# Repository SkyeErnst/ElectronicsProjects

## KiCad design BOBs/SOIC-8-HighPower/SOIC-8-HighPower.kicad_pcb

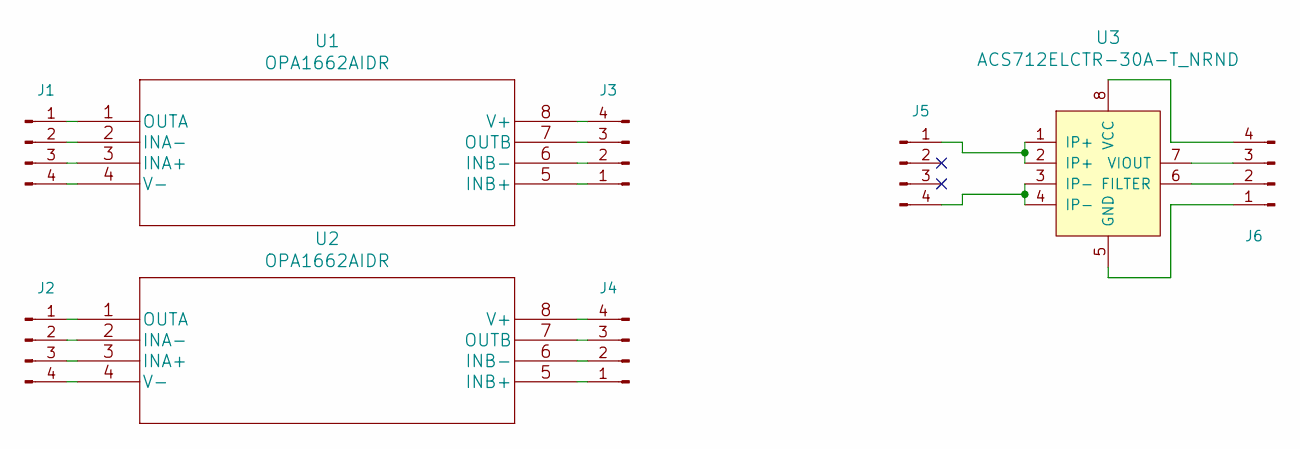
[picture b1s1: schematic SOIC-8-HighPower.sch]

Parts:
J1, J2, J3, J4, J5, J6: Conn_01x04_Male; PinHeader_1x04_P2.54mm_Vertical
U1, U2: OPA1662AIDR; SOIC-8_3.9x4.9mm_P1.27mm
U3: ACS712ELCTR-30A-T_NRND; SOIC-8_3.9x4.9mm_P1.27mm; MPN ACS712ELCTR-30A-T; Digi-Key_PN 620-1191-1-ND

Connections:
unnamed: J1.1, U1.1 (OUTA)
unnamed: J1.2, U1.2 (INA-)
unnamed: J1.3, U1.3 (INA+)
unnamed: J1.4, U1.4 (V-)
unnamed: J2.1, U2.1 (OUTA)
unnamed: J2.2, U2.2 (INA-)
unnamed: J2.3, U2.3 (INA+)
unnamed: J2.4, U2.4 (V-)
unnamed: J3.1, U1.5 (INB+)
unnamed: J3.2, U1.6 (INB-)
unnamed: J3.3, U1.7 (OUTB)
unnamed: J3.4, U1.8 (V+)
unnamed: J4.1, U2.5 (INB+)
unnamed: J4.2, U2.6 (INB-)
unnamed: J4.3, U2.7 (OUTB)
unnamed: J4.4, U2.8 (V+)
unnamed: J5.1, U3.1 (IP+), U3.2 (IP+)
unnamed: J5.4, U3.3 (IP-), U3.4 (IP-)
unnamed: J6.1, U3.5 (GND)
unnamed: J6.2, U3.6 (FILTER)
unnamed: J6.3, U3.7 (VIOUT)
unnamed: J6.4, U3.8 (VCC)

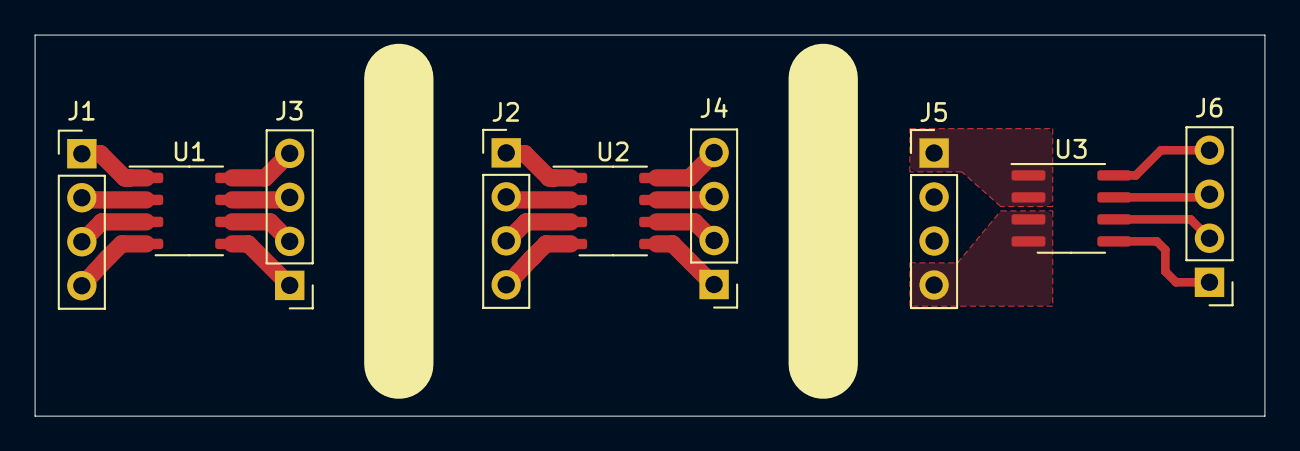
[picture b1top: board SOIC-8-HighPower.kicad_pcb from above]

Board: 2 copper layers, 71.0 x 22.0 mm, 9 parts (0 on the bottom side), 22 nets.

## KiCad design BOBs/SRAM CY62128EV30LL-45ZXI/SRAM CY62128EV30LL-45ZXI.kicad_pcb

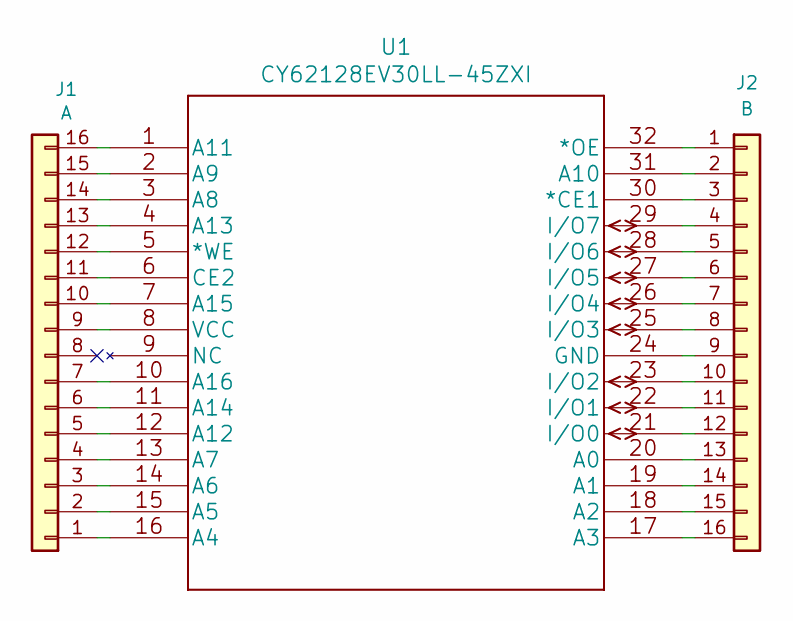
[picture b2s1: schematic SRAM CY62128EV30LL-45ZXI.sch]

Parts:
J1: A; PinHeader_1x16_P2.54mm_Vertical
J2: B; PinHeader_1x16_P2.54mm_Vertical
U1: CY62128EV30LL-45ZXI; TSOP-I-32_18.4x8mm_P0.5mm

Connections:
unnamed: J1.1, U1.16 (A4)
unnamed: J1.2, U1.15 (A5)
unnamed: J1.3, U1.14 (A6)
unnamed: J1.4, U1.13 (A7)
unnamed: J1.5, U1.12 (A12)
unnamed: J1.6, U1.11 (A14)
unnamed: J1.7, U1.10 (A16)
unnamed: J1.9, U1.8 (VCC)
unnamed: J1.10, U1.7 (A15)
unnamed: J1.11, U1.6 (CE2)
unnamed: J1.12, U1.5 (*WE)
unnamed: J1.13, U1.4 (A13)
unnamed: J1.14, U1.3 (A8)
unnamed: J1.15, U1.2 (A9)
unnamed: J1.16, U1.1 (A11)
unnamed: J2.1, U1.32 (*OE)
unnamed: J2.2, U1.31 (A10)
unnamed: J2.3, U1.30 (*CE1)
unnamed: J2.4, U1.29 (I/O7)
unnamed: J2.5, U1.28 (I/O6)
unnamed: J2.6, U1.27 (I/O5)
unnamed: J2.7, U1.26 (I/O4)
unnamed: J2.8, U1.25 (I/O3)
unnamed: J2.9, U1.24 (GND)
unnamed: J2.10, U1.23 (I/O2)
unnamed: J2.11, U1.22 (I/O1)
unnamed: J2.12, U1.21 (I/O0)
unnamed: J2.13, U1.20 (A0)
unnamed: J2.14, U1.19 (A1)
unnamed: J2.15, U1.18 (A2)
unnamed: J2.16, U1.17 (A3)

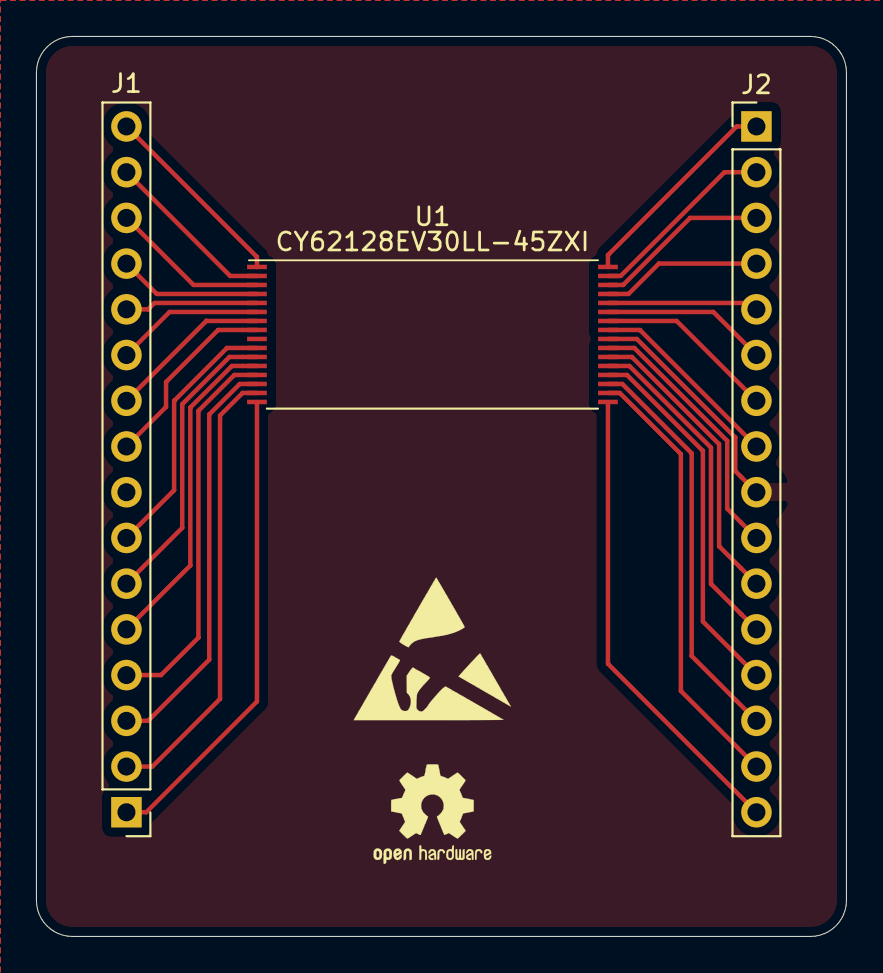
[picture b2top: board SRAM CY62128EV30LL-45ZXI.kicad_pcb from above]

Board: 2 copper layers, 45.0 x 50.0 mm, 3 parts (0 on the bottom side), 31 nets.

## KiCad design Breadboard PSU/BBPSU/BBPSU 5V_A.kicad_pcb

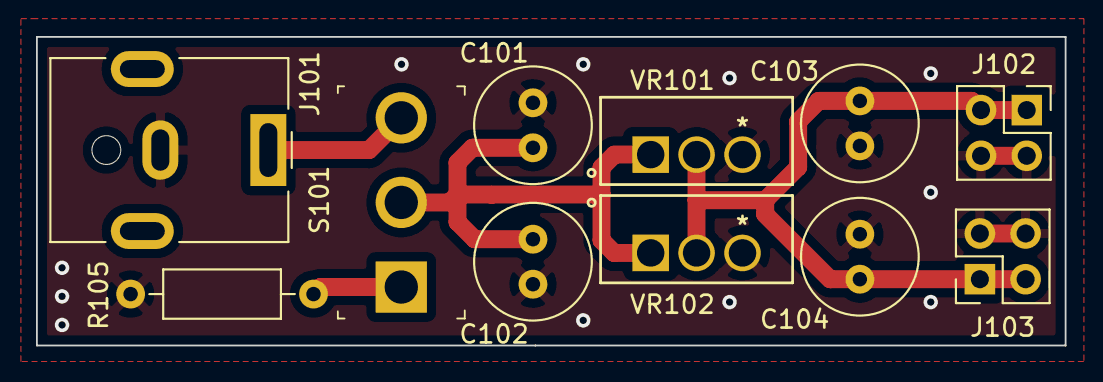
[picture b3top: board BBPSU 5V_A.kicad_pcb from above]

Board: 2 copper layers, 57.2 x 17.1 mm, 11 parts (0 on the bottom side), 5 nets.

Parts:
C101, C102: 0.33uF; C_Radial_D6.3mm_H11.0mm_P2.50mm
C103, C104: 0.1uF; C_Radial_D6.3mm_H11.0mm_P2.50mm
J101: PJ-063AH; BarrelJack_CUI_PJ-063AH_Horizontal
J102, J103: 2.54mm pitch; PinHeader_2x02_P2.54mm_Vertical
R105: 100K; R_Axial_DIN0207_L6.3mm_D2.5mm_P10.16mm_Horizontal
S101: 100SP1T1B4M2QE; Toggle_Switch_100SP1T1B4M2QE
VR101, VR102: L78S05CV

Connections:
+5V: C103.1, C104.1, J102.1, J102.3, J103.1, J103.3, VR101.2, VR102.2
/PWR_AFT_SW: C101.1, C102.1, S101.2, VR101.1, VR102.1
GND: C101.2, C102.2, C103.2, C104.2, J101.2, J102.2, J102.4, J103.2, J103.4, R105.1, VR101.3, VR102.3
unnamed: R105.2, S101.1
PWR_IN: J101.1, S101.3

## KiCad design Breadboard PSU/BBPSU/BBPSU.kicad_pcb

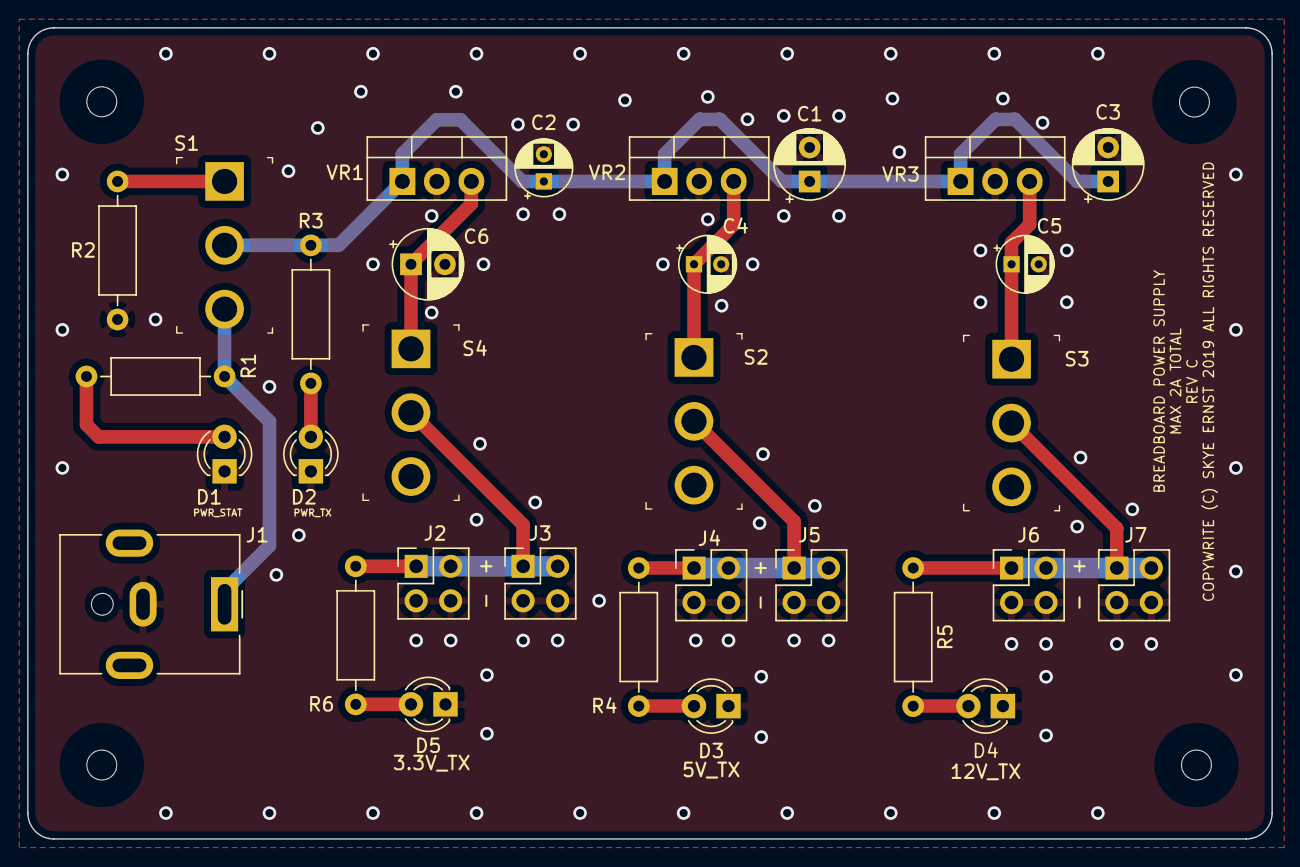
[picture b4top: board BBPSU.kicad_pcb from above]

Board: 2 copper layers, 91.6 x 59.7 mm, 31 parts (0 on the bottom side), 15 nets.

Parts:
C1, C3: 0.33uF; CP_Radial_D5.0mm_P2.50mm
C2: 10uF; CP_Radial_D4.0mm_P2.00mm
C4, C5: 0.1uF; CP_Radial_D4.0mm_P2.00mm
C6: 100uF; CP_Radial_D5.0mm_P2.50mm
D1, D2, D3, D4, D5: LED; LED_D3.0mm
J1: PJ-063AH; BarrelJack_CUI_PJ-063AH_Horizontal
J2, J3, J4, J5, J6, J7: 2.54mm pitch; PinSocket_2x02_P2.54mm_Vertical
R1: 660; R_Axial_DIN0207_L6.3mm_D2.5mm_P10.16mm_Horizontal
R2: 100K; R_Axial_DIN0207_L6.3mm_D2.5mm_P10.16mm_Horizontal
R3, R5: 680; R_Axial_DIN0207_L6.3mm_D2.5mm_P10.16mm_Horizontal
R4: 220; R_Axial_DIN0207_L6.3mm_D2.5mm_P10.16mm_Horizontal
R6: 100; R_Axial_DIN0207_L6.3mm_D2.5mm_P10.16mm_Horizontal
S1, S2, S3, S4: 100SP1T1B4M2QE; Toggle_Switch_100SP1T1B4M2QE
VR1, VR2: L78S05CV; TO-220-3_Vertical
VR3: L78S12CV; TO-220-3_Vertical

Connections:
+3V3: C6.1, S4.1, VR1.3
+5V: C4.1, S2.1, VR2.3
+12V: C5.1, S3.1, VR3.3
/POST_VR1_SW: J2.1, J2.3, J3.1, J3.3, R6.1, S4.2
/POST_VR2_SW: J4.1, J4.3, J5.1, J5.3, R4.1, S2.2
/POST_VR3_SW: J6.1, J6.3, J7.1, J7.3, R5.1, S3.2
/PWR_AFT_SW: C1.1, C2.1, C3.1, R3.2, S1.2, VR1.1, VR2.1, VR3.1
/PWR_IN: J1.1, R1.2, S1.3
GND: C1.2, C2.2, C3.2, C4.2, C5.2, C6.2, D1.1, D2.1, D3.1, D4.1, D5.1, J1.2, J2.2, J2.4, J3.2, J3.4, J4.2, J4.4, J5.2, J5.4, J6.2, J6.4, J7.2, J7.4, R2.1, VR1.2, VR2.2, VR3.2
unnamed: D1.2, R1.1
unnamed: D2.2, R3.1
unnamed: D3.2, R4.2
unnamed: D4.2, R5.2
unnamed: D5.2, R6.2
unnamed: R2.2, S1.1

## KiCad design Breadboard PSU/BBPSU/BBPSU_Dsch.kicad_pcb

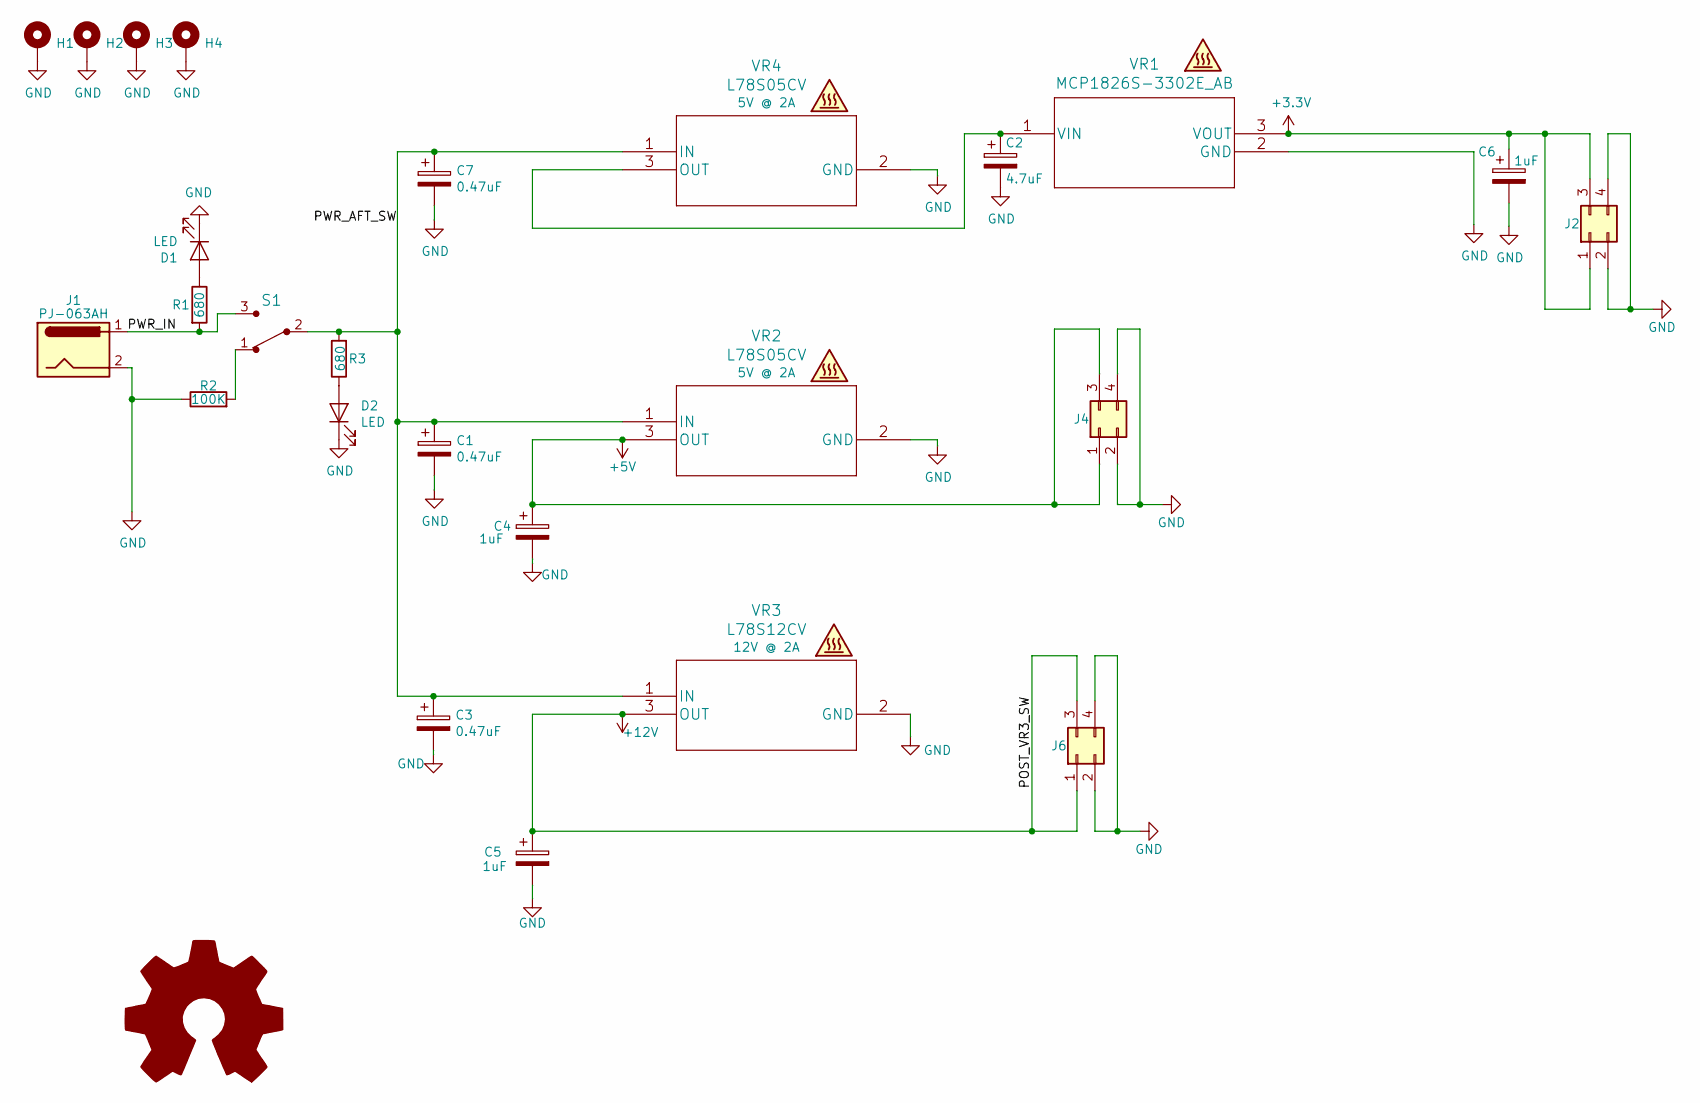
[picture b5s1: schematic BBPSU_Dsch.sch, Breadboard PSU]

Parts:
C1, C3, C7: 0.47uF; CP_Radial_D5.0mm_P2.50mm
C2: 4.7uF; CP_Radial_D4.0mm_P2.00mm
C4, C5: 1uF; CP_Radial_D4.0mm_P2.00mm
C6: 1uF; CP_Radial_D5.0mm_P2.50mm
D1, D2: LED; LED_D3.0mm
H1, H2, H3, H4: MountingHole_Pad; MountingHole_2.2mm_M2_Pad
J1: PJ-063AH; BarrelJack_CUI_PJ-063AH_Horizontal; digikey CP-063AH-ND
J2, J4, J6: 2.54mm pitch; PinSocket_2x02_P2.54mm_Vertical
R1, R3: 680; R_Axial_DIN0207_L6.3mm_D2.5mm_P10.16mm_Horizontal
R2: 100K; R_Axial_DIN0207_L6.3mm_D2.5mm_P10.16mm_Horizontal
S1: 100SP1T1B4M2QE; Toggle_Switch_100SP1T1B4M2QE; MPN 100SP1T1B4M2QE; Digi-Key_PN EG2355-ND
VR1: MCP1826S-3302E_AB; TO-220-3_Vertical
VR2, VR4: L78S05CV; TO-220-3_Vertical; digikey 497-1468-5-ND
VR3: L78S12CV; TO-220-3_Vertical; digikey 497-1469-5-ND

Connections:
+3V3: C6.1, J2.1, J2.3, VR1.3 (VOUT)
+5V: C4.1, J4.1, J4.3, VR2.3 (OUT)
+12V: C5.1, J6.1, J6.3, VR3.3 (OUT)
/PWR_AFT_SW: C1.1, C3.1, C7.1, R3.2, S1.2 (Com), VR2.1 (IN), VR3.1 (IN), VR4.1 (IN)
/PWR_IN: J1.1, R1.2, S1.3
GND: C1.2, C2.2, C3.2, C4.2, C5.2, C6.2, C7.2, D1.1 (K), D2.1 (K), H1.1, H2.1, H3.1, H4.1, J1.2, J2.2, J2.4, J4.2, J4.4, J6.2, J6.4, R2.1, VR1.2 (GND), VR2.2 (GND), VR3.2 (GND), VR4.2 (GND)
unnamed: C2.1, VR1.1 (VIN), VR4.3 (OUT)
unnamed: D1.2 (A), R1.1
unnamed: D2.2 (A), R3.1
unnamed: R2.2, S1.1

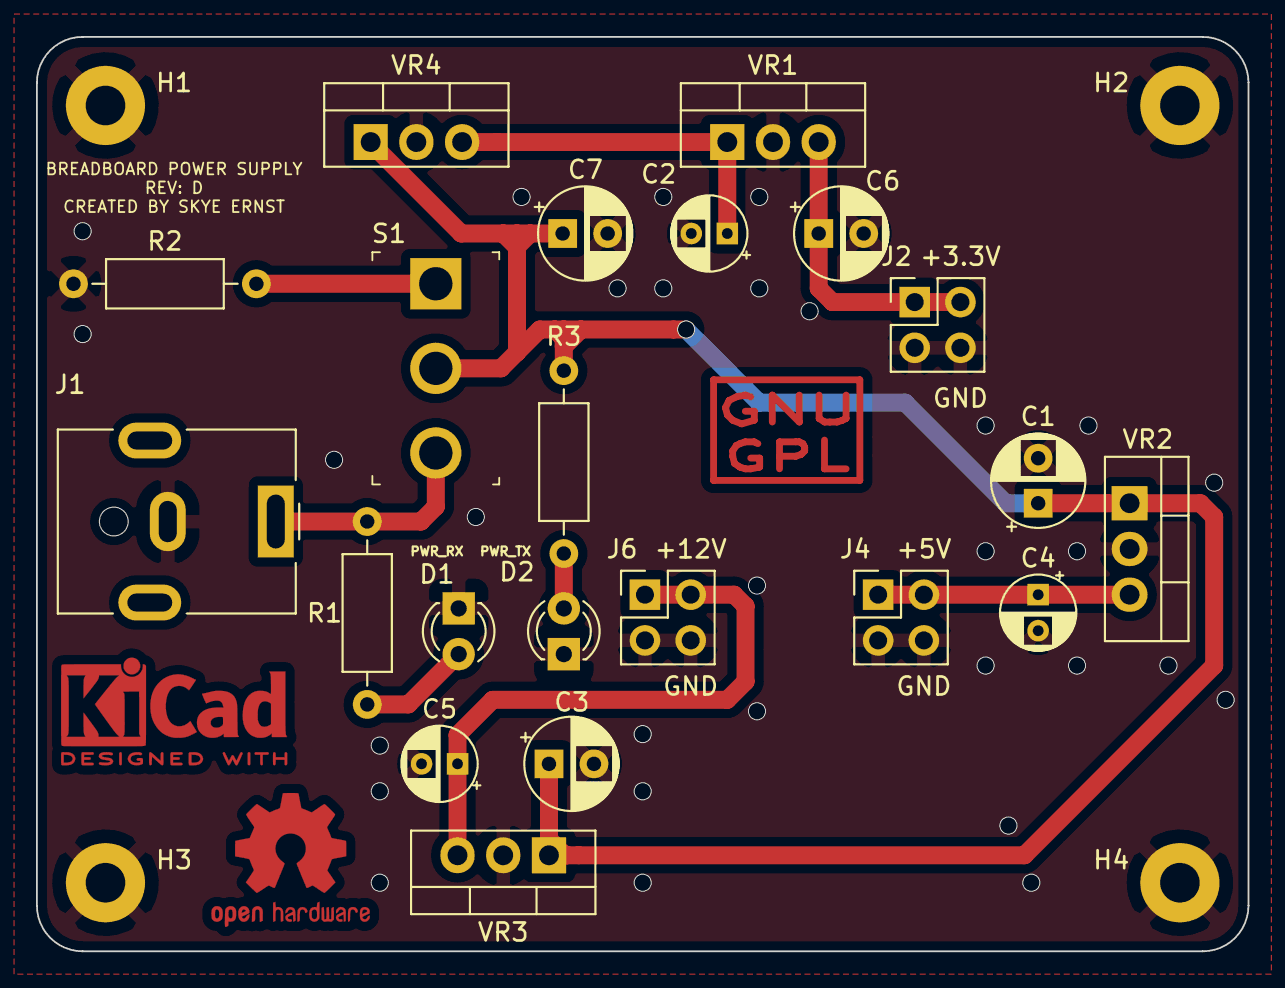
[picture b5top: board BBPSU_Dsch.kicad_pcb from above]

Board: 2 copper layers, 67.3 x 50.8 mm, 25 parts (0 on the bottom side), 10 nets.

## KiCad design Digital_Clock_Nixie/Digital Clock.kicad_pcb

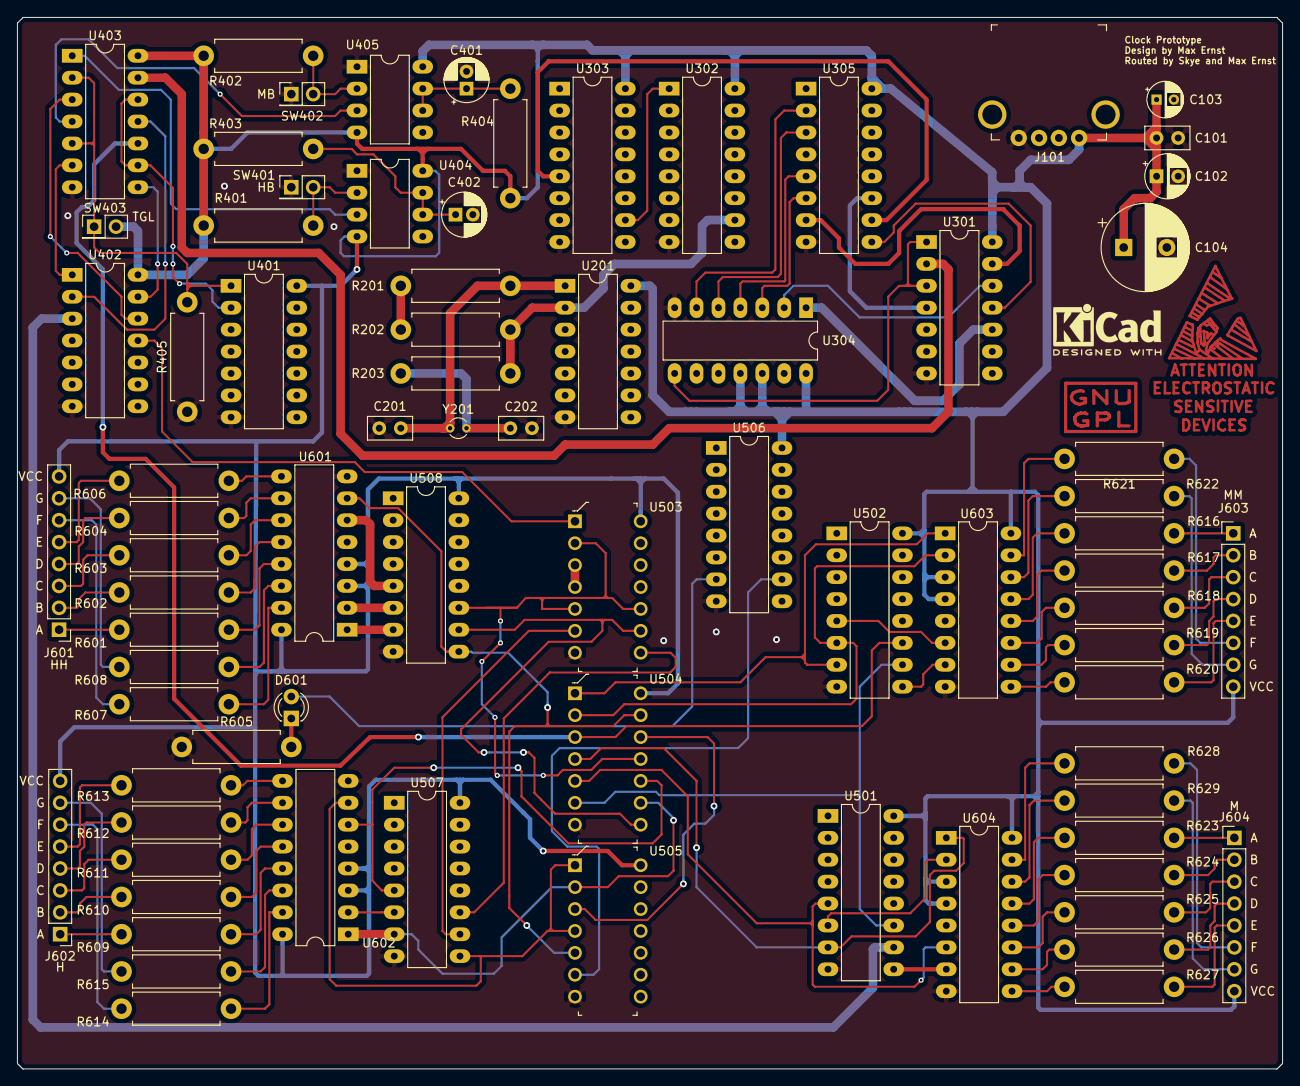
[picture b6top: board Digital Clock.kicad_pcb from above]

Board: 2 copper layers, 146.7 x 121.9 mm, 78 parts (0 on the bottom side), 116 nets.

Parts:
C101: 100nF; C_Disc_D5.0mm_W2.5mm_P2.50mm
C102: 1uF; CP_Radial_D5.0mm_P2.50mm
C103: 47uF; CP_Radial_D4.0mm_P2.00mm
C104: 1000uF; CP_Radial_D10.0mm_P5.00mm
C201, C202: 22pF; C_Disc_D5.0mm_W2.5mm_P2.50mm
C401, C402: 0.22uF; CP_Radial_D5.0mm_P2.00mm
D601: GREEN; LED_D3.0mm
J101: USB_A; USB_A_Female_UE27AC54100
J601, J602, J603, J604: Conn_01x08; PinHeader_1x08_P2.54mm_Vertical
R201, R202: 6.5Meg; R_Axial_DIN0411_L9.9mm_D3.6mm_P12.70mm_Horizontal
R203: 270k; R_Axial_DIN0411_L9.9mm_D3.6mm_P12.70mm_Horizontal
R401, R402, R405: 1k; R_Axial_DIN0411_L9.9mm_D3.6mm_P12.70mm_Horizontal
R403, R404: 1Meg; R_Axial_DIN0411_L9.9mm_D3.6mm_P12.70mm_Horizontal
R601, R602, R603, R604, R606, R607, R608, R609, R610, R611, R612, R613, R614, R615, R616, R617, R618, R619, R620, R621, R622, R623, R624, R625, R626, R627, R628, R629: 24; R_Axial_DIN0411_L9.9mm_D3.6mm_P12.70mm_Horizontal
R605: 220; R_Axial_DIN0411_L9.9mm_D3.6mm_P12.70mm_Horizontal
SW401: Hour_Button; PinHeader_2x01_P2.54mm_Vertical
SW402: Minute_Button; PinHeader_2x01_P2.54mm_Vertical
SW403: Toggle_Switch; PinHeader_2x01_P2.54mm_Vertical
U201: 74HCU04E; DIP-14_W7.62mm_LongPads
U301, U401: 74S04; DIP-14_W7.62mm_LongPads
U302, U303, U305: SN74HC4040N; DIP-16_W7.62mm_LongPads
U304: CD74HC30E; DIP-14_W7.62mm_LongPads
U402: SN74LS32N; DIP-14_W7.62mm_LongPads
U403: SN74HCT08N; DIP-14_W7.62mm_LongPads
U404, U405: NE555; DIP-8_W7.62mm_LongPads
U501, U502, U506, U507, U508: 4040; DIP-16_W7.62mm_LongPads
U503: SN74LS32N; DIP-14_W3mm
U504: SN74LS08N; DIP-14_W3mm
U505: SN74ALS08N; DIP-14_W3mm
U601, U602, U603, U604: 7447; DIP-16_W7.62mm_LongPads
Y201: 32.768kHz; Crystal_Round_D2.0mm_Vertical

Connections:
+5V: C101.1, C102.1, C103.1, C104.1, J101.1, J601.8, J602.8, J603.8, J604.8, R401.2, R402.2, R403.1, R404.1, SW403.2, U201.14, U301.14, U302.16, U303.16, U304.11, U304.12, U304.14, U305.16, U401.14, U402.14, U403.14, U404.4, U404.8, U405.4, U405.8, U501.16, U502.16, U503.14, U504.14, U505.14, U506.16, U507.16, U508.16, U601.3, U601.4, U601.16, U602.3, U602.4, U602.16, U603.3, U603.4, U603.16, U604.3, U604.4, U604.16
/ButtonLogic/1stPlaceHoursInput: U402.11, U503.1
/ButtonLogic/1stPlaceMinutesInput: U402.3, U501.10
/ButtonLogic/MinutesOutput: U403.10, U502.11, U504.3
/ButtonLogic/SecondsOutput: U301.2, U403.13
/DisplaySection/1stP_HH_O: U504.13, U505.5, U508.9, U601.7
/DisplaySection/1stP_H_O: U505.1, U505.4, U507.9, U602.7
/DisplaySection/1stP_MM_O: U502.9, U603.7
/DisplaySection/1stP_M_O: U501.9, U604.7
/DisplaySection/2ndP_HH_O: U508.7, U601.1
/DisplaySection/2ndP_H_O: U504.9, U505.2, U507.7, U602.1
/DisplaySection/2ndP_MM_O: U502.7, U504.1, U603.1
/DisplaySection/2ndP_M_O: U501.7, U504.4, U604.1
/DisplaySection/3rdP_HH_O: U508.6, U601.2
/DisplaySection/3rdP_H_O: U507.6, U602.2
/DisplaySection/3rdP_MM_O: U502.6, U504.2, U603.2
/DisplaySection/3rdP_M_O: U501.6, U604.2
/DisplaySection/4thP_HH_O: U508.5, U601.6
/DisplaySection/4thP_H_O: U504.10, U507.5, U602.6
/DisplaySection/4thP_MM_O: U502.5, U603.6
/DisplaySection/4thP_M_O: U501.5, U504.5, U604.6
/DisplaySection/AM_PM_INDICATOR: D601.2, U506.7
/Oscillator/Oscillator32768Output: R202.1, R203.1, U201.2, U302.10
GND: C101.2, C102.2, C103.2, C104.2, C201.2, C202.2, C401.2, C402.2, J101.4, R405.1, R605.1, SW401.1, SW402.1, U201.7, U301.7, U302.8, U303.8, U304.7, U305.8, U401.7, U402.7, U403.7, U404.1, U405.1, U501.8, U502.8, U503.7, U504.7, U505.7, U506.8, U507.8, U508.8, U601.8, U602.8, U603.8, U604.8
unnamed: C201.1, R201.2, U201.1, Y201.1
unnamed: C202.1, R203.2, Y201.2
unnamed: C401.1, R404.2, U405.6, U405.7
unnamed: C402.1, R403.2, U404.6, U404.7
unnamed: D601.1, R605.2
unnamed: J601.1, R601.1
unnamed: J601.2, R602.1
unnamed: J601.3, R603.1
unnamed: J601.4, R604.1
unnamed: J601.5, R606.1
unnamed: J601.6, R607.1
unnamed: J601.7, R608.1
unnamed: J602.1, R609.1
unnamed: J602.2, R610.1
unnamed: J602.3, R611.1
unnamed: J602.4, R612.1
unnamed: J602.5, R613.1
unnamed: J602.6, R614.1
unnamed: J602.7, R615.1
unnamed: J603.1, R616.1
unnamed: J603.2, R617.1
unnamed: J603.3, R618.1
unnamed: J603.4, R619.1
unnamed: J603.5, R620.1
unnamed: J603.6, R621.1
unnamed: J603.7, R622.1
unnamed: J604.1, R623.1
unnamed: J604.2, R624.1
unnamed: J604.3, R625.1
unnamed: J604.4, R626.1
unnamed: J604.5, R627.1
unnamed: J604.6, R628.1
unnamed: J604.7, R629.1
unnamed: R201.1, R202.2
unnamed: R401.1, SW401.2, U404.2
unnamed: R402.1, SW402.2, U405.2
unnamed: R405.2, SW403.1, U401.1, U403.2, U403.5
unnamed: R601.2, U601.13
unnamed: R602.2, U601.12
unnamed: R603.2, U601.11
unnamed: R604.2, U601.10
unnamed: R606.2, U601.9
unnamed: R607.2, U601.15
unnamed: R608.2, U601.14
unnamed: R609.2, U602.13
unnamed: R610.2, U602.12
unnamed: R611.2, U602.11
unnamed: R612.2, U602.10
unnamed: R613.2, U602.9
unnamed: R614.2, U602.15
unnamed: R615.2, U602.14
unnamed: R616.2, U603.13
unnamed: R617.2, U603.12
unnamed: R618.2, U603.11
unnamed: R619.2, U603.10
unnamed: R620.2, U603.9
unnamed: R621.2, U603.15
unnamed: R622.2, U603.14
unnamed: R623.2, U604.13
unnamed: R624.2, U604.12
unnamed: R625.2, U604.11
unnamed: R626.2, U604.10
unnamed: R627.2, U604.9
unnamed: R628.2, U604.15
unnamed: R629.2, U604.14
unnamed: U301.1, U301.3, U304.8
unnamed: U301.4, U305.11
unnamed: U301.10, U304.1
unnamed: U301.11, U305.9
unnamed: U301.12, U304.2
unnamed: U301.13, U305.7
unnamed: U302.1, U303.10
unnamed: U303.5, U305.10
unnamed: U304.3, U305.6
unnamed: U304.4, U305.5
unnamed: U304.5, U305.3
unnamed: U304.6, U305.2
unnamed: U401.2, U403.9, U403.12
unnamed: U402.1, U403.6
unnamed: U402.2, U403.11
unnamed: U402.12, U403.3
unnamed: U402.13, U403.8
unnamed: U403.1, U404.3
unnamed: U403.4, U405.3
unnamed: U501.11, U502.10, U504.6
unnamed: U503.3, U503.4
unnamed: U503.6, U507.10
unnamed: U503.8, U507.11
unnamed: U503.9, U504.8, U508.10
unnamed: U503.2, U503.5, U503.10, U504.11, U508.11
unnamed: U504.12, U505.3
unnamed: U505.6, U506.10

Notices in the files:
Breadboard PSU/BBPSU/BBPSU 5V_A.kicad_pcb:
COPYRIGHT (c) SKYE ERNST 2019
ALL RIGHTS RESERVED
Breadboard PSU/BBPSU/BBPSU.kicad_pcb:
COPYWRITE (C) SKYE ERNST 2019 ALL RIGHTS RESERVED
parts and their libraries:
Copyright 2016 Accelerated Designs. All rights reserved.
